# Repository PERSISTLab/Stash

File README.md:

# Stash: Flexible Energy Storage for Intermittent Sensors

This repository hosts a reference Stash implementation as a peripheral for <a href="https://github.com/PERSISTLab/FlickerPlatform">the Flicker hardware platform</a>

Batteryless sensors promise a sustainable future for sensing, but they face significant challenges when storing and using
environmental energy. Incoming energy can fluctuate unpredictably between periods of scarcity and abundance, and device
performance depends on both incoming energy and how much a device can store. Existing batteryless devices have used fixed
or run-time selectable front-end capacitor banks to meet the energy needs of different tasks. Neither approach adapts well to
rapidly changing energy harvesting conditions, nor does it allow devices to store excess energy during times of abundance
without sacrificing performance.

Stash, a hardware back-end energy storage technique that allows batteryless devices to charge quickly
and store excess energy when it is abundant, extending their operating time and carrying out additional tasks without
compromising the main ones. Stash performs like a small capacitor device when small capacitors excel and like a large
capacitor device when large capacitors excel, with no additional software complexity and negligible power overhead. We
evaluate Stash using two applications—temperature sensing and wearable activity monitoring—under both synthetic solar
energy and recorded solar and thermal traces from various human activities. Our results show that Stash increased sensor
coverage by up to 15% under variable energy-harvesting conditions when compared to competitor configurations that used
fixed small, large, and reconfigurable front-end energy storage.

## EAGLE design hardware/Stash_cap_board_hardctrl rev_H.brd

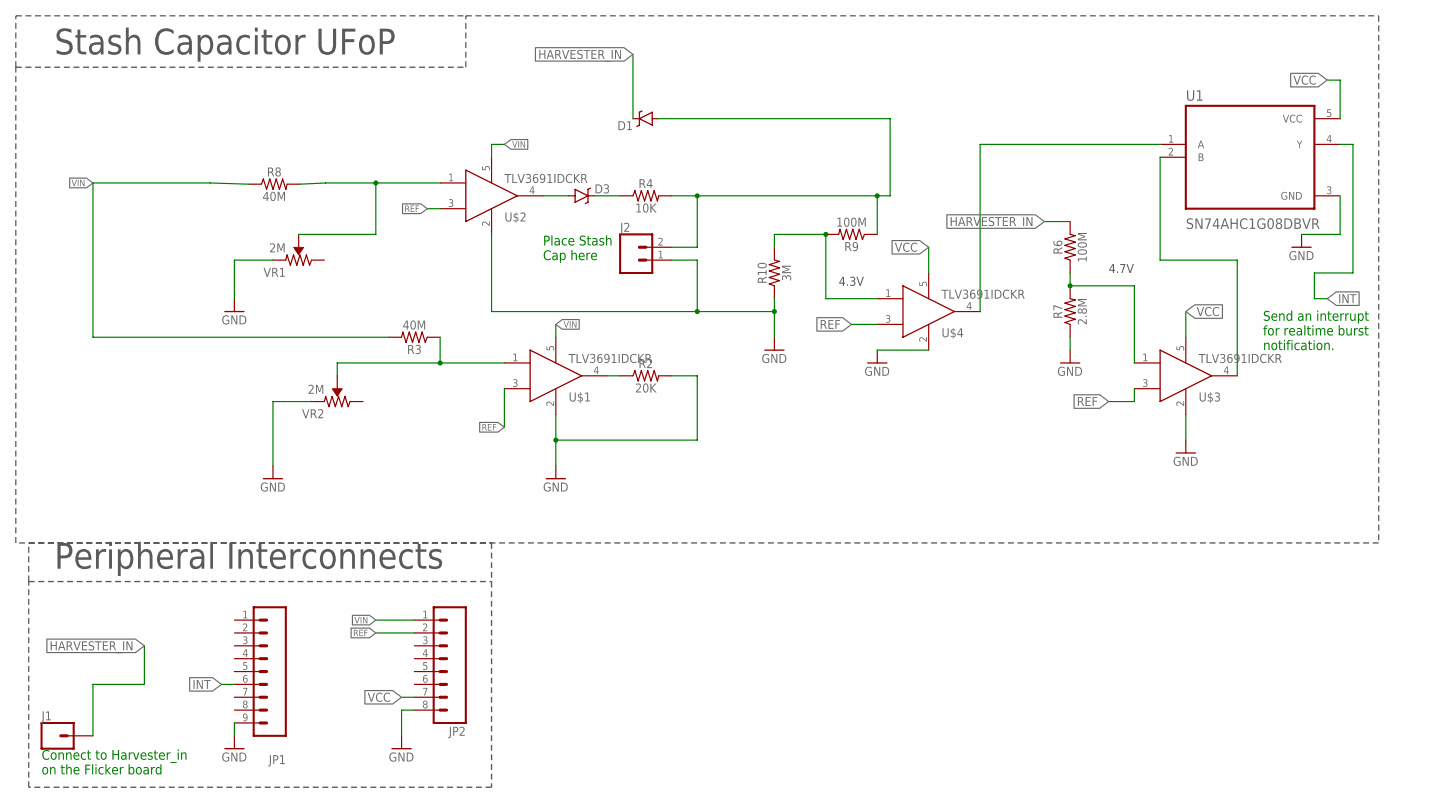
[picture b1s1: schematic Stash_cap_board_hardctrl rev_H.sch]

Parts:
D1, D3: RB751; SOD-523; MPN BAS40-02V-V-G-08; DIGIKEY BAS40-02V-V-G-08GICT-ND
J1: CONN_01; 1X01
J2: CONN_02; 1X02
JP1: M091.27MM; 1X09-1.27MM; MANUFACTURERPARTNUMBER GRPB091VWVN-RC; DIGIKEY S9014E-09-ND
JP2: M081.27MM; 1X08-1.27MM; MANUFACTURERPARTNUMBER GRPB081VWVN-RC; DIGIKEY S9014E-08-ND
R2: 20K; 0805
R3, R8: 40M; 0805
R4: 10K; 0603
R6, R9: 100M; 0805
R7: 2.8M; 0805
R10: 3M; 0805
U1: SN74AHC1G08DBVR; SOT95P280X145-5N
U$1, U$2, U$3, U$4: TLV3691IDCKR; SOT353
VR1, VR2: 2M; TRIMPOT-SMD-3MM-CLOSED

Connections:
CAP_VCC: D1.A, J2.2, R4.2, R9.1
GND: J2.1, JP1.9, JP2.8, R2.2, R7.1, R10.1, U1.3 (GND), U$1.2, U$2.2, U$3.2, U$4.2, VR1.1 (CCW), VR2.1 (CCW)
HARVESTER_IN: D1.C, J1.1, R6.2
INT: JP1.6, U1.4 (Y)
unnamed: D3.A, U$2.4
unnamed: R2.1, U$1.4
unnamed: R8.2, U$2.1, VR1.2 (WIPER)
unnamed: R3.1, U$1.1, VR2.2 (WIPER)
unnamed: R6.1, R7.2, U$3.1
unnamed: D3.C, R4.1
unnamed: R9.2, R10.2, U$4.1
unnamed: U1.2 (B), U$3.4
unnamed: U1.1 (A), U$4.4
REF: JP2.2, U$1.3, U$2.3, U$3.3, U$4.3
VCC: JP2.7, U1.5 (VCC), U$3.5, U$4.5
VIN: JP2.1, R3.2, R8.1, U$1.5, U$2.5

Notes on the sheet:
Peripheral Interconnects
Stash Capacitor UFoP
4.7V
4.3V
Send an interrupt for realtime burst notification.
Connect to Harvester_in on the Flicker board
Place Stash Cap here

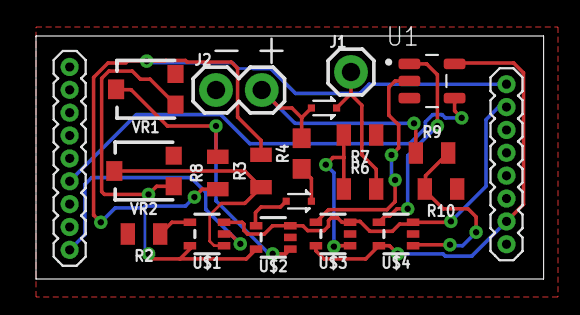
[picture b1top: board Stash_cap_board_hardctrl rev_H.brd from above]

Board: 2 copper layers, 28.2 x 13.5 mm, 21 parts (0 on the bottom side), 16 nets.

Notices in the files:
parts and their libraries:
SparkFun-DiscreteSemi: Licensing: CC v3.0 Share-Alike You are welcome to use this library for commercial purposes.
SparkFun-Connectors: Licensing: Creative Commons ShareAlike 4.0 International - https://creativecommons.org/licenses/by-sa/4.0
